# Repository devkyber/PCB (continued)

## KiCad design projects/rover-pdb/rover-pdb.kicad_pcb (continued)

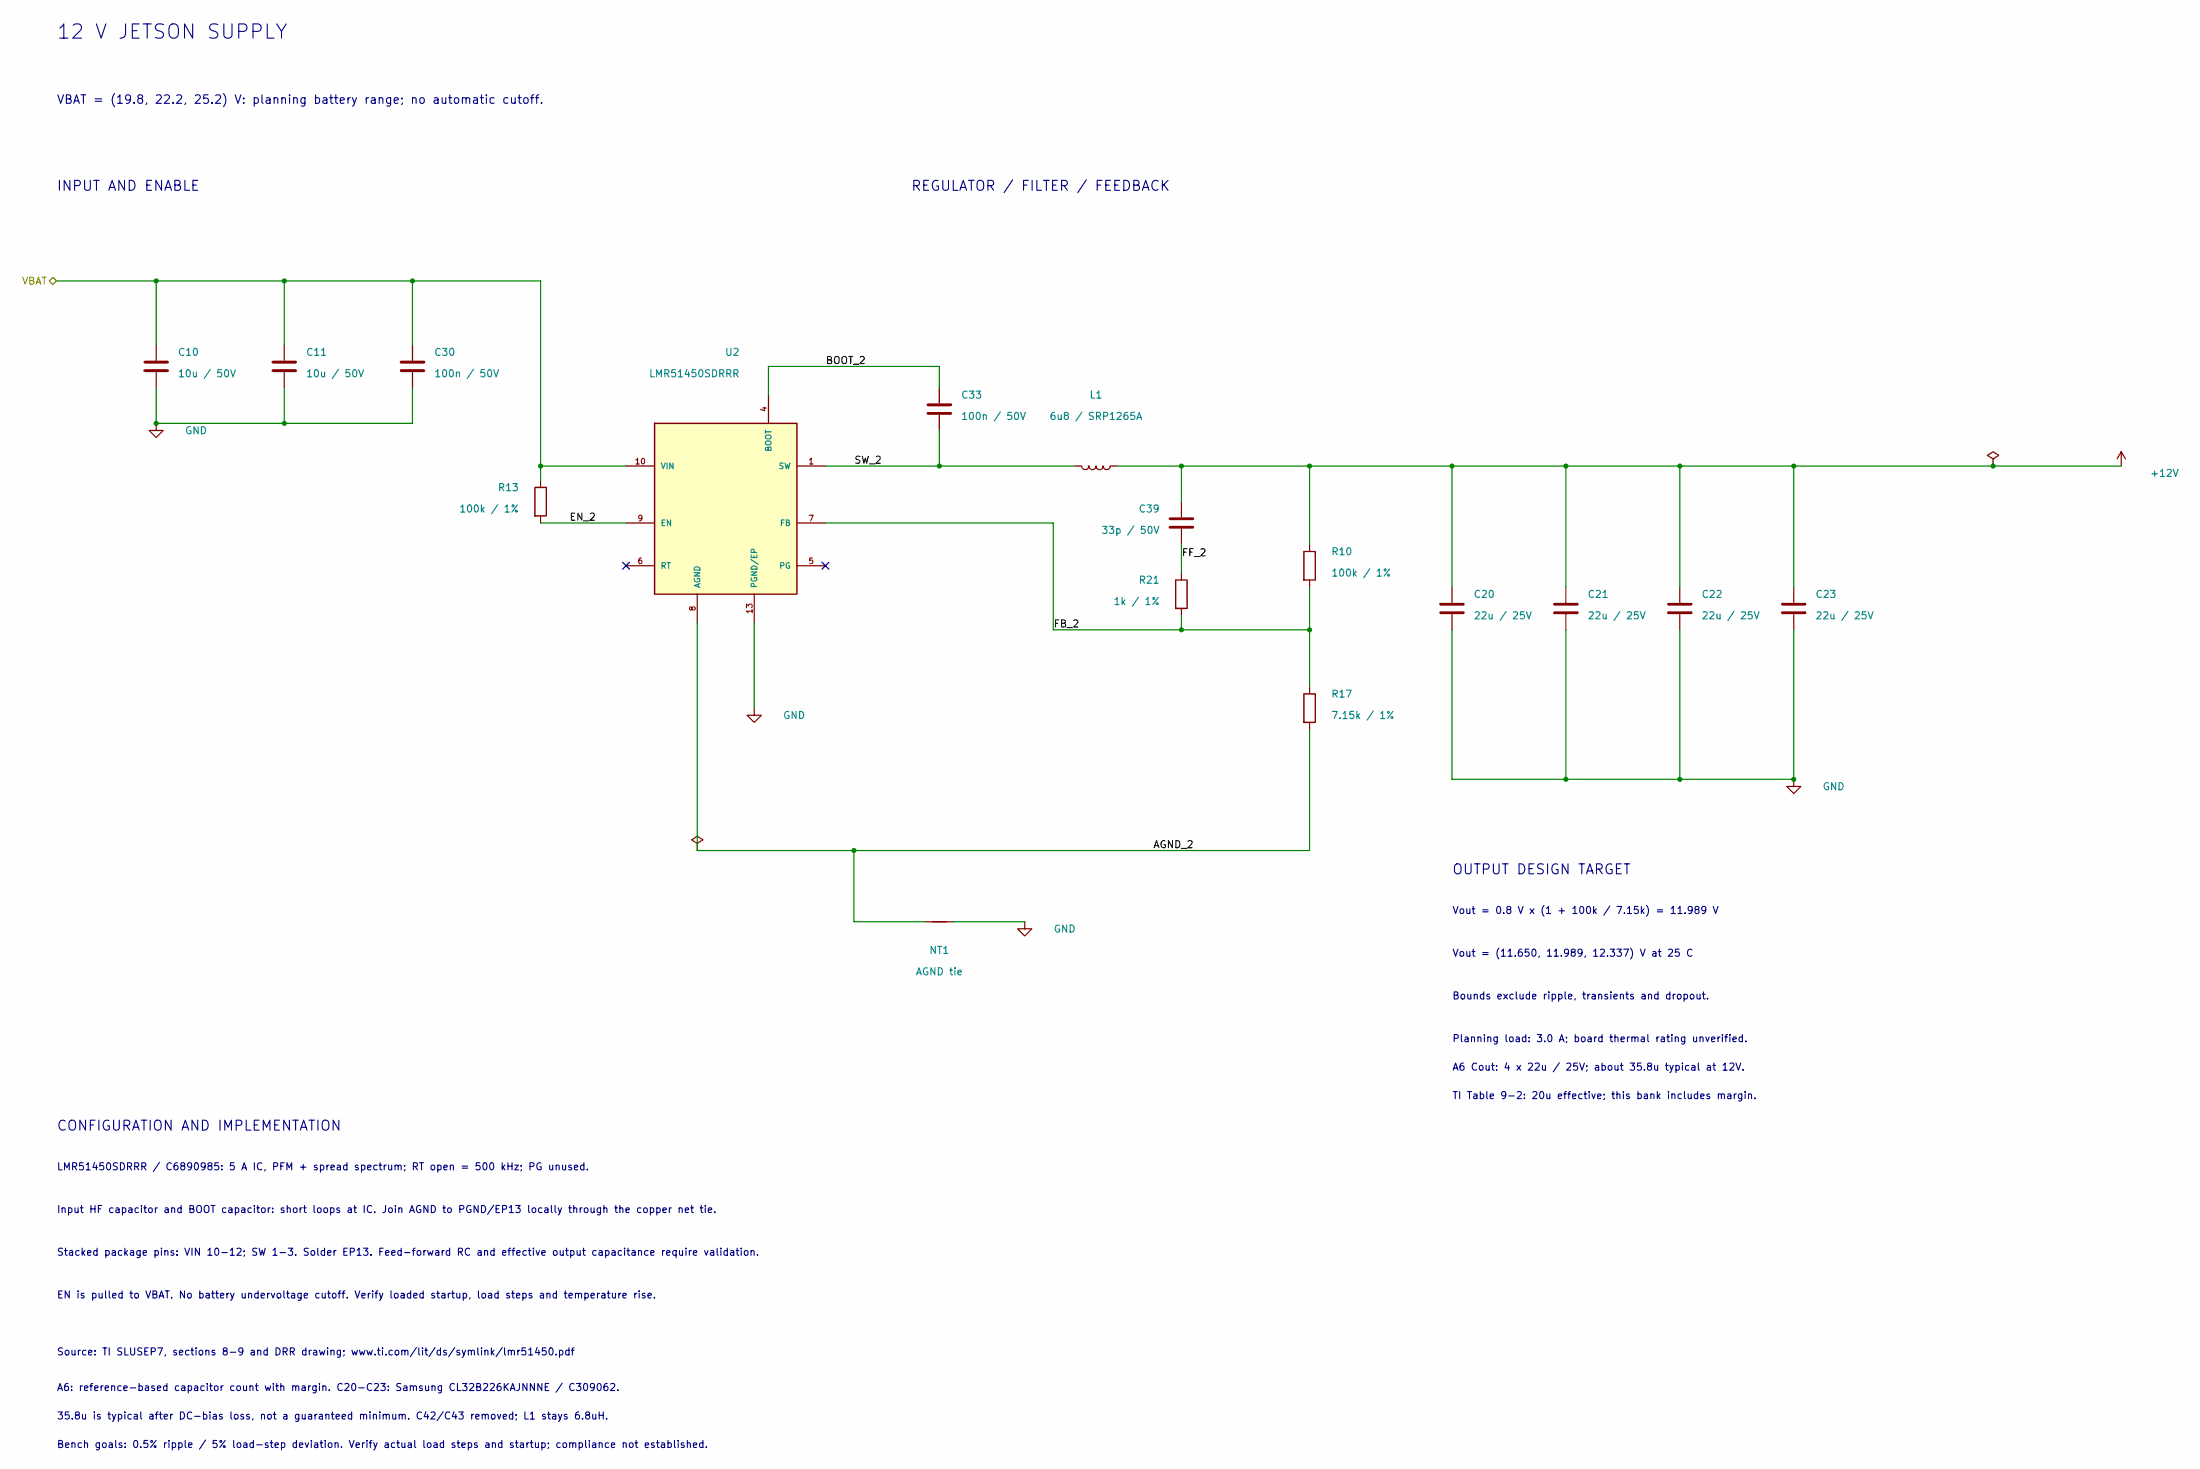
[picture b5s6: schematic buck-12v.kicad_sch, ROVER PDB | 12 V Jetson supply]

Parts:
C10, C11: 10u / 50V; C_1210_3225Metric; MPN GRM32ER71H106KA12L; LCSC Part C77102
C20, C21, C22, C23: 22u / 25V; C_1210_3225Metric; MPN CL32B226KAJNNNE; LCSC Part C309062
C30, C33: 100n / 50V; C_0805_2012Metric; MPN CL21B104KBCNNNC; LCSC Part C1711
C39: 33p / 50V; C_0603_1608Metric; MPN CL10C330JB8NNNC; LCSC Part C1663
L1: 6u8 / SRP1265A; SRP1265A_LeadFrame_13.5x12.5_P11.1; MPN SRP1265A-6R8M; LCSC Part C2041326
NT1: AGND tie; AGND_Tie_LMR51450
R10, R13: 100k / 1%; R_0805_2012Metric; MPN RC0805FR-07100KL; LCSC Part C96346
R17: 7.15k / 1%; R_0805_2012Metric; MPN 0805W8F7151T5E; LCSC Part C17806
R21: 1k / 1%; R_0805_2012Metric; MPN 0805W8F1001T5E; LCSC Part C17513
U2: LMR51450SDRRR; LMR51450_DRR_WSON12_3x3; MPN LMR51450SDRRR; LCSC Part C6890985

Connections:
+12V: C20.1, C21.1, C22.1, C23.1, C39.1, L1.1, R10.1; also elsewhere on the board
/12 V Jetson supply/AGND_2: NT1.1, R17.2, U2.8 (AGND)
/12 V Jetson supply/BOOT_2: C33.1, U2.4 (BOOT)
/12 V Jetson supply/EN_2: R13.2, U2.9 (EN)
/12 V Jetson supply/FB_2: R10.2, R17.1, R21.2, U2.7 (FB)
/12 V Jetson supply/FF_2: C39.2, R21.1
/12 V Jetson supply/SW_2: C33.2, L1.2, U2.1 (SW), U2.2 (SW), U2.3 (SW)
/VBAT: C10.1, C11.1, C30.1, R13.1, U2.10 (VIN), U2.11 (VIN), U2.12 (VIN); also elsewhere on the board
GND: C10.2, C11.2, C20.2, C21.2, C22.2, C23.2, C30.2, NT1.2, U2.13 (PGND/EP); also elsewhere on the board

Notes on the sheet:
Bounds exclude ripple, transients and dropout.
REGULATOR / FILTER / FEEDBACK
35.8u is typical after DC-bias loss, not a guaranteed minimum. C42/C43 removed; L1 stays 6.8uH.
EN is pulled to VBAT. No battery undervoltage cutoff. Verify loaded startup, load steps and temperature rise.
CONFIGURATION AND IMPLEMENTATION
A6 Cout: 4 x 22u / 25V; about 35.8u typical at 12V.
Vout = (11.650, 11.989, 12.337) V at 25 C
Bench goals: 0.5% ripple / 5% load-step deviation. Verify actual load steps and startup; compliance not established.
OUTPUT DESIGN TARGET
Vout = 0.8 V x (1 + 100k / 7.15k) = 11.989 V
A6: reference-based capacitor count with margin. C20-C23: Samsung CL32B226KAJNNNE / C309062.
INPUT AND ENABLE
Source: TI SLUSEP7, sections 8-9 and DRR drawing; www.ti.com/lit/ds/symlink/lmr51450.pdf
LMR51450SDRRR / C6890985: 5 A IC, PFM + spread spectrum; RT open = 500 kHz; PG unused.
12 V JETSON SUPPLY
VBAT = (19.8, 22.2, 25.2) V: planning battery range; no automatic cutoff.
Planning load: 3.0 A; board thermal rating unverified.
TI Table 9-2: 20u effective; this bank includes margin.
Stacked package pins: VIN 10-12; SW 1-3. Solder EP13. Feed-forward RC and effective output capacitance require validation.
Input HF capacitor and BOOT capacitor: short loops at IC. Join AGND to PGND/EP13 locally through the copper net tie.

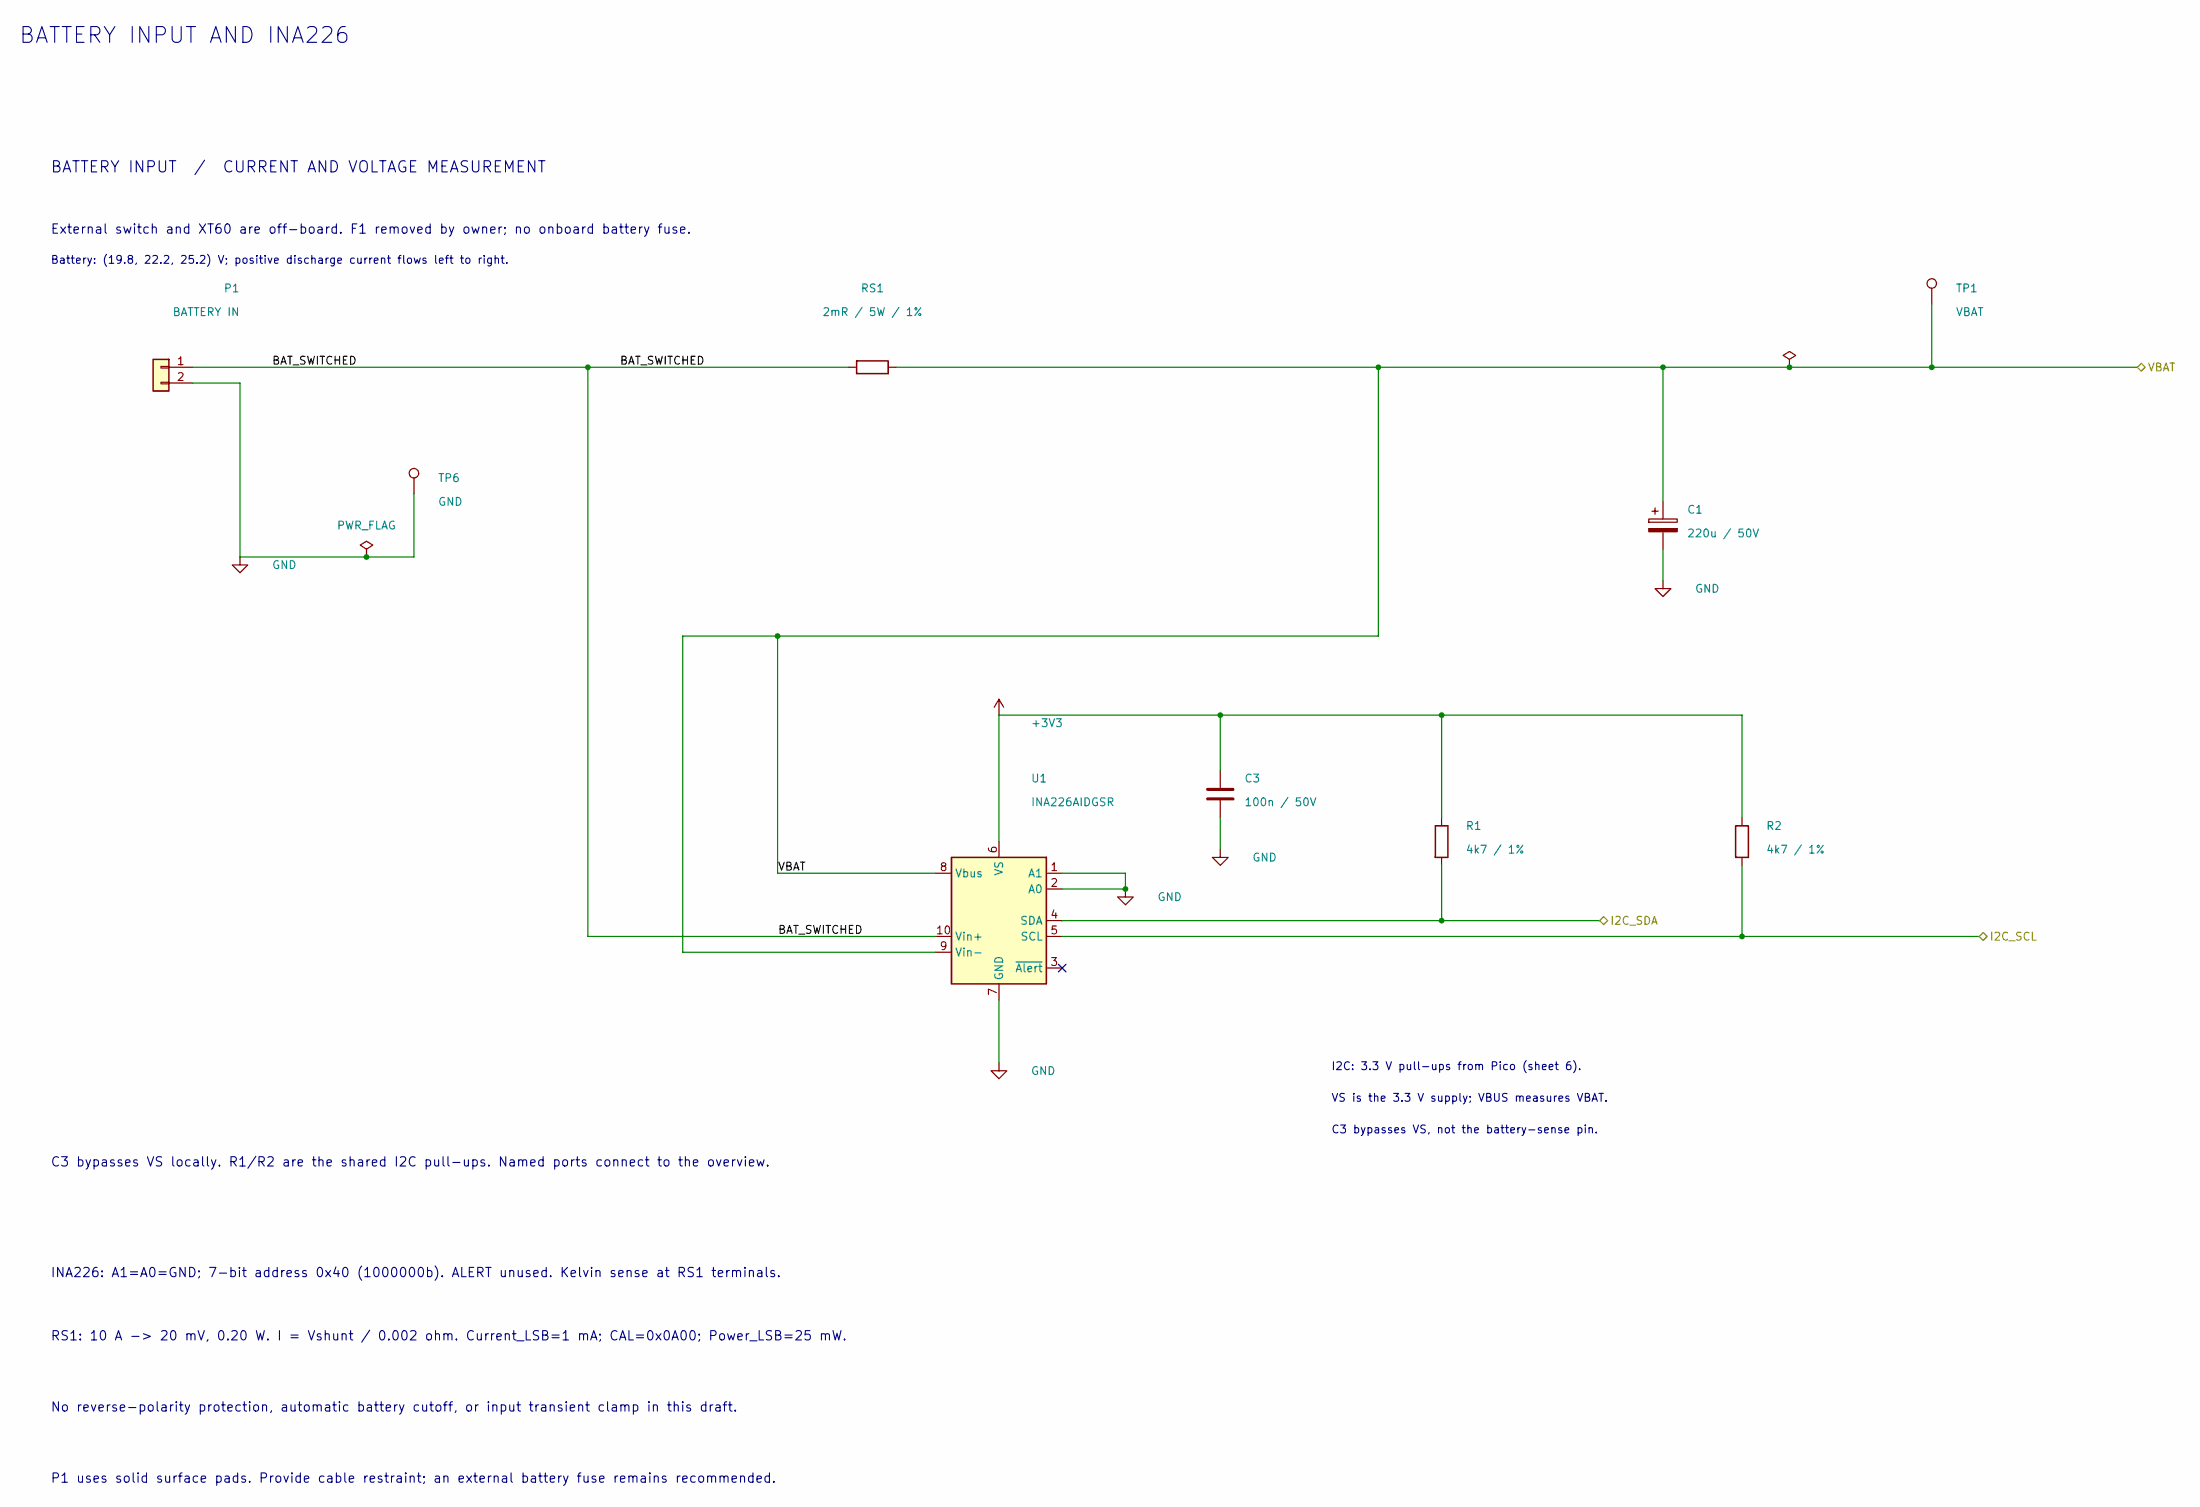
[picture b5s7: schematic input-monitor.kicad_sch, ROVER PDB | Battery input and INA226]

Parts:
C1: 220u / 50V; CP_Radial_D10.0mm_P5.00mm; MPN EEU-FR1H221B; LCSC Part C1579630
C3: 100n / 50V; C_0805_2012Metric; MPN CL21B104KBCNNNC; LCSC Part C1711
P1: BATTERY IN; WirePads_2_6x8_P12; MPN BATTERY IN
R1, R2: 4k7 / 1%; R_0805_2012Metric; MPN RC0805FR-074K7L; LCSC Part C60816
RS1: 2mR / 5W / 1%; CSS2H_2512_6.35x3.05; MPN CSS2H-2512K-2L00F; LCSC Part C2093761
TP1: VBAT; TestPoint_Pad_D2.0mm; MPN VBAT
TP6: GND; TestPoint_Pad_D2.0mm; MPN GND
U1: INA226AIDGSR; MSOP-10_3x3mm_P0.5mm; MPN INA226AIDGSR; LCSC Part C49851

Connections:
+3V3: C3.1, R1.1, R2.1, U1.6 (VS); also elsewhere on the board
/Battery input and INA226/BAT_SWITCHED: P1.1, RS1.2, U1.10 (Vin+)
/Battery input and INA226/I2C_SCL: R2.2, U1.5 (SCL); also elsewhere on the board
/Battery input and INA226/I2C_SDA: R1.2, U1.4 (SDA); also elsewhere on the board
/VBAT: C1.1, RS1.1, TP1.1 (1_1), U1.8 (Vbus), U1.9 (Vin-); also elsewhere on the board
GND: C1.2, C3.2, P1.2, TP6.1 (1_1), U1.1 (A1), U1.2 (A0), U1.7 (GND); also elsewhere on the board

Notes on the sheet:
RS1: 10 A -> 20 mV, 0.20 W. I = Vshunt / 0.002 ohm. Current_LSB=1 mA; CAL=0x0A00; Power_LSB=25 mW.
INA226: A1=A0=GND; 7-bit address 0x40 (1000000b). ALERT unused. Kelvin sense at RS1 terminals.
BATTERY INPUT AND INA226
C3 bypasses VS locally. R1/R2 are the shared I2C pull-ups. Named ports connect to the overview.
Battery: (19.8, 22.2, 25.2) V; positive discharge current flows left to right.
No reverse-polarity protection, automatic battery cutoff, or input transient clamp in this draft.
I2C: 3.3 V pull-ups from Pico (sheet 6).
C3 bypasses VS, not the battery-sense pin.
External switch and XT60 are off-board. F1 removed by owner; no onboard battery fuse.
BATTERY INPUT / CURRENT AND VOLTAGE MEASUREMENT
P1 uses solid surface pads. Provide cable restraint; an external battery fuse remains recommended.
VS is the 3.3 V supply; VBUS measures VBAT.

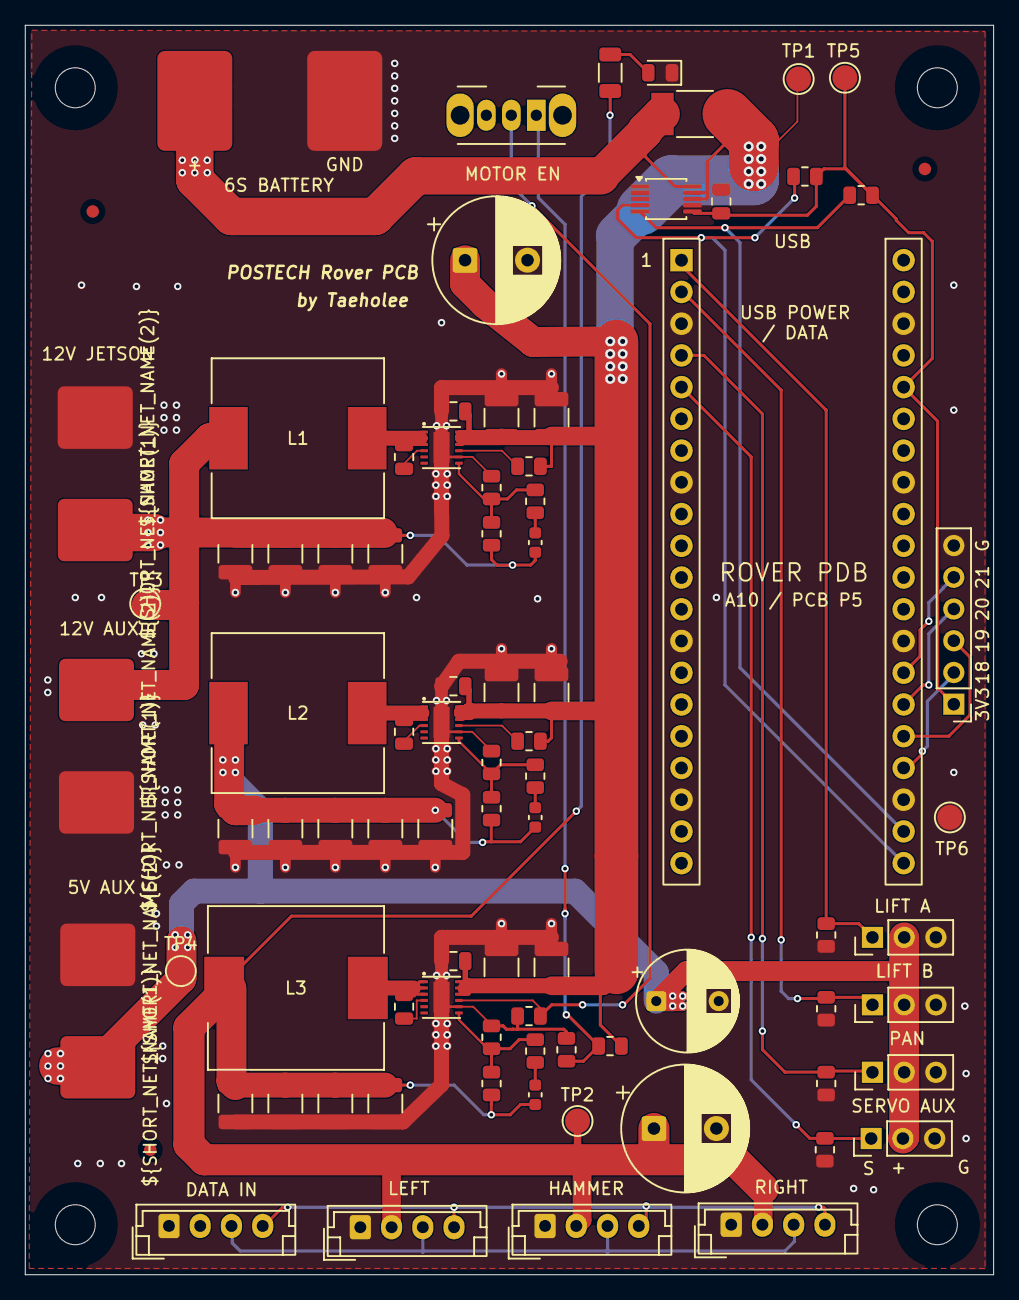
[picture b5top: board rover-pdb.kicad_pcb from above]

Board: 2 copper layers, 77.5 x 100.0 mm, 93 parts (0 on the bottom side), 39 nets.

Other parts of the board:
FID1, FID2, FID3: Fiducial; Fiducial_1mm_Mask2mm
H1, H2, H3, H4: MountingHole_3.2mm_M3

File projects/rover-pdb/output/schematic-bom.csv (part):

Reference,Value,MPN,LCSC,Footprint,DNP,InBOM,Sheet
C1,220u / 50V,EEU-FR1H221B,C1579630,Capacitor_THT:CP_Radial_D10.0mm_P5.00mm,no,yes,input-monitor.kicad_sch
C2,470u / 16V,EEU-FR1C471B,C1579437,Capacitor_THT:CP_Radial_D8.0mm_P5.00mm,no,yes,pico-servos.kicad_sch
C3,100n / 50V,CL21B104KBCNNNC,C1711,Capacitor_SMD:C_0805_2012Metric,no,yes,input-monitor.kicad_sch
C5,220u / 50V,EEU-FR1H221B,C1579630,Capacitor_THT:CP_Radial_D10.0mm_P5.00mm,no,yes,buck-motor.kicad_sch
C10,10u / 50V,GRM32ER71H106KA12L,C77102,Capacitor_SMD:C_1210_3225Metric,no,yes,buck-12v.kicad_sch
C11,10u / 50V,GRM32ER71H106KA12L,C77102,Capacitor_SMD:C_1210_3225Metric,no,yes,buck-12v.kicad_sch
C12,10u / 50V,GRM32ER71H106KA12L,C77102,Capacitor_SMD:C_1210_3225Metric,no,yes,buck-5v.kicad_sch
C13,10u / 50V,GRM32ER71H106KA12L,C77102,Capacitor_SMD:C_1210_3225Metric,no,yes,buck-5v.kicad_sch
C14,10u / 50V,GRM32ER71H106KA12L,C77102,Capacitor_SMD:C_1210_3225Metric,no,yes,buck-motor.kicad_sch
C15,10u / 50V,GRM32ER71H106KA12L,C77102,Capacitor_SMD:C_1210_3225Metric,no,yes,buck-motor.kicad_sch
C16,10u / 50V,GRM32ER71H106KA12L,C77102,Capacitor_SMD:C_1210_3225Metric,no,yes,buck-motor.kicad_sch
C17,10u / 50V,GRM32ER71H106KA12L,C77102,Capacitor_SMD:C_1210_3225Metric,no,yes,buck-motor.kicad_sch
C18,10u / 50V,GRM32ER71H106KA12L,C77102,Capacitor_SMD:C_1210_3225Metric,no,yes,buck-motor.kicad_sch
C19,10u / 50V,GRM32ER71H106KA12L,C77102,Capacitor_SMD:C_1210_3225Metric,no,yes,buck-motor.kicad_sch
C20,22u / 25V,CL32B226KAJNNNE,C309062,Capacitor_SMD:C_1210_3225Metric,no,yes,buck-12v.kicad_sch
C21,22u / 25V,CL32B226KAJNNNE,C309062,Capacitor_SMD:C_1210_3225Metric,no,yes,buck-12v.kicad_sch
C22,22u / 25V,CL32B226KAJNNNE,C309062,Capacitor_SMD:C_1210_3225Metric,no,yes,buck-12v.kicad_sch
C23,22u / 25V,CL32B226KAJNNNE,C309062,Capacitor_SMD:C_1210_3225Metric,no,yes,buck-12v.kicad_sch
C24,22u / 25V,CL32B226KAJNNNE,C309062,Capacitor_SMD:C_1210_3225Metric,no,yes,buck-5v.kicad_sch
C25,22u / 25V,CL32B226KAJNNNE,C309062,Capacitor_SMD:C_1210_3225Metric,no,yes,buck-5v.kicad_sch
C26,22u / 25V,CL32B226KAJNNNE,C309062,Capacitor_SMD:C_1210_3225Metric,no,yes,buck-5v.kicad_sch
C27,22u / 25V,CL32B226KAJNNNE,C309062,Capacitor_SMD:C_1210_3225Metric,no,yes,buck-5v.kicad_sch
C28,22u / 25V,CL32B226KAJNNNE,C309062,Capacitor_SMD:C_1210_3225Metric,no,yes,buck-5v.kicad_sch
C30,100n / 50V,CL21B104KBCNNNC,C1711,Capacitor_SMD:C_0805_2012Metric,no,yes,buck-12v.kicad_sch
C31,100n / 50V,CL21B104KBCNNNC,C1711,Capacitor_SMD:C_0805_2012Metric,no,yes,buck-5v.kicad_sch
C32,100n / 50V,CL21B104KBCNNNC,C1711,Capacitor_SMD:C_0805_2012Metric,no,yes,buck-motor.kicad_sch
C33,100n / 50V,CL21B104KBCNNNC,C1711,Capacitor_SMD:C_0805_2012Metric,no,yes,buck-12v.kicad_sch
C34,100n / 50V,CL21B104KBCNNNC,C1711,Capacitor_SMD:C_0805_2012Metric,no,yes,buck-5v.kicad_sch
C35,100n / 50V,CL21B104KBCNNNC,C1711,Capacitor_SMD:C_0805_2012Metric,no,yes,buck-motor.kicad_sch
C39,33p / 50V,CL10C330JB8NNNC,C1663,Capacitor_SMD:C_0603_1608Metric,no,yes,buck-12v.kicad_sch
C40,33p / 50V,CL10C330JB8NNNC,C1663,Capacitor_SMD:C_0603_1608Metric,no,yes,buck-5v.kicad_sch
C41,33p / 50V,CL10C330JB8NNNC,C1663,Capacitor_SMD:C_0603_1608Metric,no,yes,buck-motor.kicad_sch
D2,GREEN,KT-0805G,C2297,rover:KT0805G_0805_A1_K2,no,yes,buck-motor.kicad_sch
J1,U2D2 DATA IN,B4B-EH-A(LF)(SN),C160258,Connector_JST:JST_EH_B4B-EH-A_1x04_P2.50mm_Vertical,no,yes,dxl-enable.kicad_sch
J2,LIFT A,TSW-103-07-G-S,C3335811,Connector_PinHeader_2.54mm:PinHeader_1x03_P2.54mm_Vertical,no,yes,pico-servos.kicad_sch
J3,LIFT B,TSW-103-07-G-S,C3335811,Connector_PinHeader_2.54mm:PinHeader_1x03_P2.54mm_Vertical,no,yes,pico-servos.kicad_sch
J4,CAMERA PAN,TSW-103-07-G-S,C3335811,Connector_PinHeader_2.54mm:PinHeader_1x03_P2.54mm_Vertical,no,yes,pico-servos.kicad_sch
J5,LEFT WHEELS,B4B-EH-A(LF)(SN),C160258,Connector_JST:JST_EH_B4B-EH-A_1x04_P2.50mm_Vertical,no,yes,dxl-enable.kicad_sch
J6,RIGHT WHEELS,B4B-EH-A(LF)(SN),C160258,Connector_JST:JST_EH_B4B-EH-A_1x04_P2.50mm_Vertical,no,yes,dxl-enable.kicad_sch
J7,HAMMER,B4B-EH-A(LF)(SN),C160258,Connector_JST:JST_EH_B4B-EH-A_1x04_P2.50mm_Vertical,no,yes,dxl-enable.kicad_sch
J9,EXP / DNP,2.54-1x6P直针,C37208,Connector_PinHeader_2.54mm:PinHeader_1x06_P2.54mm_Vertical,yes,yes,pico-servos.kicad_sch
L1,6u8 / SRP1265A,SRP1265A-6R8M,C2041326,rover:SRP1265A_LeadFrame_13.5x12.5_P11.1,no,yes,buck-12v.kicad_sch
L2,4u7 / SRP1265A,SRP1265A-4R7M,C780205,rover:SRP1265A_LeadFrame_13.5x12.5_P11.1,no,yes,buck-5v.kicad_sch
L3,3u3 / SRP1265A,SRP1265A-3R3M,C1329348,rover:SRP1265A_LeadFrame_13.5x12.5_P11.1,no,yes,buck-motor.kicad_sch
NT1,AGND tie,,,rover:AGND_Tie_LMR51450,no,no,buck-12v.kicad_sch
NT2,AGND tie,,,rover:AGND_Tie_LMR51450,no,no,buck-5v.kicad_sch
NT3,AGND tie,,,rover:AGND_Tie_LMR51450,no,no,buck-motor.kicad_sch
P1,BATTERY IN,BATTERY IN,,rover:WirePads_2_6x8_P12,no,no,input-monitor.kicad_sch
P2,JETSON / BARREL,JETSON / BARREL,,rover:WirePads_2_5x6_P9,no,no,pico-servos.kicad_sch
P3,12V EXP / UNWIRED,12V EXP / UNWIRED,,rover:WirePads_2_5x6_P9,no,no,pico-servos.kicad_sch
P4,5V EXP / UNWIRED,5V EXP / UNWIRED,,rover:WirePads_2_5x6_P9,no,no,pico-servos.kicad_sch
R1,4k7 / 1%,RC0805FR-074K7L,C60816,Resistor_SMD:R_0805_2012Metric,no,yes,input-monitor.kicad_sch
R2,4k7 / 1%,RC0805FR-074K7L,C60816,Resistor_SMD:R_0805_2012Metric,no,yes,input-monitor.kicad_sch
R3,10k,RC0805FR-0710KL,C84376,Resistor_SMD:R_0805_2012Metric,no,yes,pico-servos.kicad_sch
R4,10k,RC0805FR-0710KL,C84376,Resistor_SMD:R_0805_2012Metric,no,yes,pico-servos.kicad_sch
R5,10k,RC0805FR-0710KL,C84376,Resistor_SMD:R_0805_2012Metric,no,yes,pico-servos.kicad_sch
R10,100k / 1%,RC0805FR-07100KL,C96346,Resistor_SMD:R_0805_2012Metric,no,yes,buck-12v.kicad_sch
R11,100k / 1%,RC0805FR-07100KL,C96346,Resistor_SMD:R_0805_2012Metric,no,yes,buck-5v.kicad_sch
R12,100k / 1%,RC0805FR-07100KL,C96346,Resistor_SMD:R_0805_2012Metric,no,yes,buck-motor.kicad_sch
R13,100k / 1%,RC0805FR-07100KL,C96346,Resistor_SMD:R_0805_2012Metric,no,yes,buck-12v.kicad_sch
R14,100k / 1%,RC0805FR-07100KL,C96346,Resistor_SMD:R_0805_2012Metric,no,yes,buck-5v.kicad_sch
R15,100k / 1%,RC0805FR-07100KL,C96346,Resistor_SMD:R_0805_2012Metric,no,yes,buck-motor.kicad_sch
R16,19.1k / 1%,0805W8F1912T5E,C17508,Resistor_SMD:R_0805_2012Metric,no,yes,buck-5v.kicad_sch
R17,7.15k / 1%,0805W8F7151T5E,C17806,Resistor_SMD:R_0805_2012Metric,no,yes,buck-12v.kicad_sch
R18,3.74k / 1%,0805W8F3741T5E,C65649,Resistor_SMD:R_0805_2012Metric,no,yes,buck-motor.kicad_sch
R19,100k / 1%,RC0805FR-07100KL,C96346,Resistor_SMD:R_0805_2012Metric,no,yes,buck-motor.kicad_sch
R20,3k9 / 0.25W,RC1206FR-073K9L,C137289,Resistor_SMD:R_1206_3216Metric,no,yes,buck-motor.kicad_sch
R21,1k / 1%,0805W8F1001T5E,C17513,Resistor_SMD:R_0805_2012Metric,no,yes,buck-12v.kicad_sch
R22,1k / 1%,0805W8F1001T5E,C17513,Resistor_SMD:R_0805_2012Metric,no,yes,buck-5v.kicad_sch
R23,1k / 1%,0805W8F1001T5E,C17513,Resistor_SMD:R_0805_2012Metric,no,yes,buck-motor.kicad_sch
R24,22k / 1%,0805W8F2202T5E,C17560,Resistor_SMD:R_0805_2012Metric,no,yes,buck-motor.kicad_sch
RS1,2mR / 5W / 1%,CSS2H-2512K-2L00F,C2093761,rover:CSS2H_2512_6.35x3.05,no,yes,input-monitor.kicad_sch
SKT1,Pico 2 / 2x20 sockets,Pico 2,,rover:Pico2_Sockets_LXWCONN_254PM_1x20,no,yes,pico-servos.kicad_sch
SW1,MOTOR ENABLE,OS102011MA1QN1,C226259,Button_Switch_THT:SW_Slide_SPDT_Angled_CK_OS102011MA1Q,no,yes,buck-motor.kicad_sch
TP1,VBAT,VBAT,,TestPoint:TestPoint_Pad_D2.0mm,no,no,input-monitor.kicad_sch
TP2,VMOTOR,VMOTOR,,TestPoint:TestPoint_Pad_D2.0mm,no,no,buck-motor.kicad_sch
TP3,+12V,+12V,,TestPoint:TestPoint_Pad_D2.0mm,no,no,pico-servos.kicad_sch
TP4,+5V,+5V,,TestPoint:TestPoint_Pad_D2.0mm,no,no,pico-servos.kicad_sch
TP5,+3V3,+3V3,,TestPoint:TestPoint_Pad_D2.0mm,no,no,pico-servos.kicad_sch
TP6,GND,GND,,TestPoint:TestPoint_Pad_D2.0mm,no,no,input-monitor.kicad_sch
U1,INA226AIDGSR,INA226AIDGSR,C49851,Package_SO:MSOP-10_3x3mm_P0.5mm,no,yes,input-monitor.kicad_sch
U2,LMR51450SDRRR,LMR51450SDRRR,C6890985,rover:LMR51450_DRR_WSON12_3x3,no,yes,buck-12v.kicad_sch
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
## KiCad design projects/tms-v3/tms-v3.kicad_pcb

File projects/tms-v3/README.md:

# TMS v3: rework starting point

Open [tms-v3.kicad_pro](tms-v3.kicad_pro). The saved seven-sheet schematic and
PCB are the owner's current files. The 2026-10-07 workspace cleanup preserved
their bytes and established the audit below; no circuit or routing repair was
applied. Read [requirements](REQUIREMENTS.md), [design basis](DESIGN_BASIS.md),
[deviations](DEVIATIONS.md), [reference review](REFERENCE_REVIEW.md) and
[review profile](review-profile.yaml) before choosing the next change.

## Current audit: 2026-10-07

The [full shared review](docs/review/records/rework-baseline-20261007.json)
reports seven passing checks and seven blockers. The
[native ERC report](docs/review/records/erc-20261007.json) preserves the individual
findings. These reports describe saved CAD, not an approved design.

| Check | Result |
| --- | --- |
| Source integrity | Research and archived datasheets pass |
| ERC | 2 disconnected-pin errors and 3 dangling-wire warnings; 37 unspecified-pin warnings excluded by the existing policy |
| Saved connectivity snapshot | Stale for two components; current schematic and PCB disagree |
| Forward annotation | PCB schematic links are absent; ordinary F8 updating is not yet a safe handover |
| Native DRC | 1 error, 15 warnings and 4 unconnected items in both refilled runs |
| Independent manufacturing baseline | 244 errors and 4 unconnected items against the dated JLCPCB profile; includes settings, annular-ring, clearance and silk findings |
| Assembly contract | J1/J2 have conflicting values without exact MPN identity |
| Routing topology | 55 short-track and 3 covered-track advisories; these require local inspection, not automatic deletion |
| Human decisions | 0/12 current decisions, including the two mandatory shared items |

## Visual inspection of the saved schematic

All seven native PDF pages were inspected at full-page and circuit scale on
2026-10-07. This is author inspection, not an owner's release decision.
The exact render and its source hashes are recorded in
[visual provenance](docs/review/records/visual-baseline-20261007.json).

| Sheet | Remaining presentation issues |
| --- | --- |
| Overview | Six small hierarchy boxes occupy a narrow column on a mostly empty A1 page; there is no readable system-level power/interface flow or load summary |
| Power and protection | Power assertions are detached; some wiring visually approaches terminals without agreeing with native connectivity; assumptions are absent |
| Load cell / ADS1256 | Bypass, reference, clock and interface groups rely on matching detached labels; pin arrangement follows the package rather than the signal flow |
| Pressure / ADS1220 | Input and interface parts are remote from the IC; bypass parts use detached rail groups; most of the sheet is unused |
| Controller and telemetry | Long socket pin lists and labels dominate; bypass parts and the power assertion are detached; module/interface roles need clearer grouping |
| Ignition control | Sparse groups and labels make page flow difficult to follow; native ERC reports an unresolved disconnected terminal; no functional change was made |
| External connectors and test | Connectors and test points are separated into label lists; destination context and documented electrical assumptions are missing |

Titles and hierarchy are present. That does not establish readability or
electrical agreement. Follow the shared Gala/Gross conventions for any authorized
presentation work, and prove unchanged native pin/net and explicit-NC membership.

## Continue from this state

The [2026-10-07 pipeline validation](docs/review/pipeline-validation-20261007.md)
ran 25 CLI commands on disposable copies through research, import, native
previews, blocked application, review, sign-off preparation, release and cleanup.
The expected blocking and preservation checks passed. TMS remains blocked;
J1/J2 part identity prevents even a completed quotation preview. The report
states which successful export/publication paths could not be reached.

First reconcile which saved circuit is intended before updating the netmap or
PCB links. A drawing-only edit cannot silently repair a circuit discrepancy.
Then prepare a scoped native candidate and inspect every changed sheet using
the [shared workflow](../../docs/WORKFLOW.md). Do not replay the old intent over
owner edits, discard routing or silence findings by broadening deviations.

The original PDR and Rev D BOM remain historical requirements evidence, not
current production instructions. The open engineering decisions remain in the
existing requirements/profile; the cleanup and this audit resolve none of them.
Layout, assembly and release stay blocked pending their respective checks.

```powershell
uv run pcb-copilot status projects/tms-v3
uv run pcb-copilot research projects/tms-v3 --verify
uv run pcb-copilot review projects/tms-v3
```

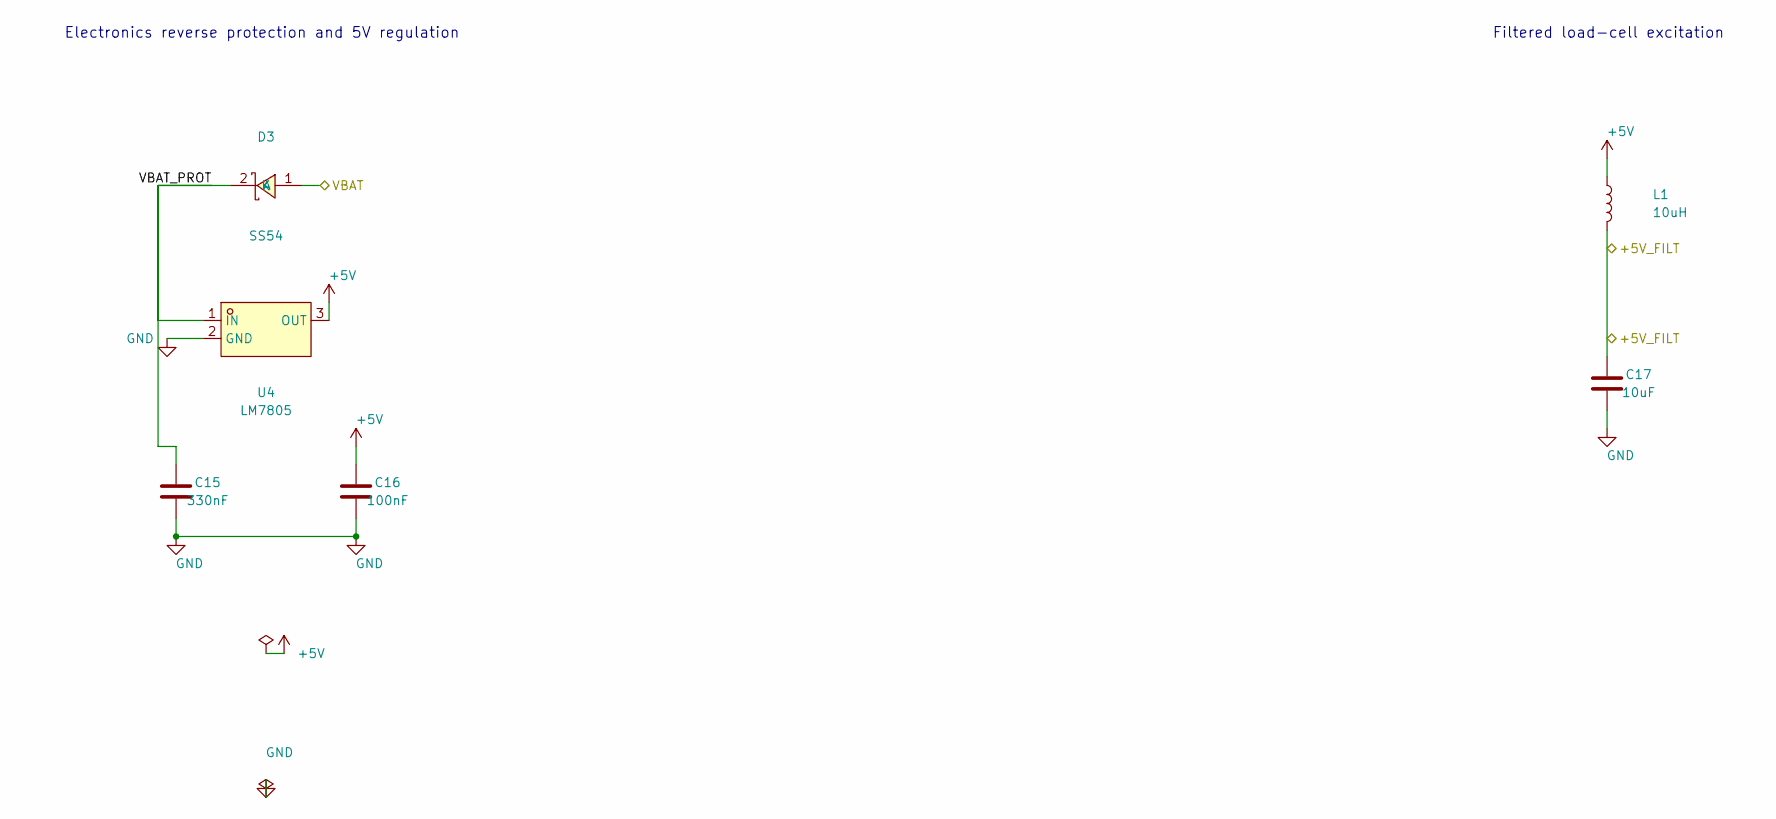
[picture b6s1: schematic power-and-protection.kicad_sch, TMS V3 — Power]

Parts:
C15: 330nF; C_0603_1608Metric
C16: 100nF; C_0603_1608Metric
C17: 10uF; C_0805_2012Metric
D3: SS54; SMA_L4.4-W2.8-LS5.4-R-RD
L1: 10uH; L_0805_2012Metric
U4: LM7805; TO-263-2_L10.1-W9.1-P5.08-LS15.2-BR-1

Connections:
+5V: C16.1, L1.1, U4.3 (OUT); also elsewhere on the board
+5V_FILT: C17.1, L1.2; also elsewhere on the board
GND: C15.2, C16.2, C17.2, U4.2 (GND); also elsewhere on the board
Power/VBAT_PROT: C15.1, D3.2 (K), U4.1 (IN)
VBAT: D3.1 (A); also elsewhere on the board

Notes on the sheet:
Electronics reverse protection and 5V regulation
Filtered load-cell excitation

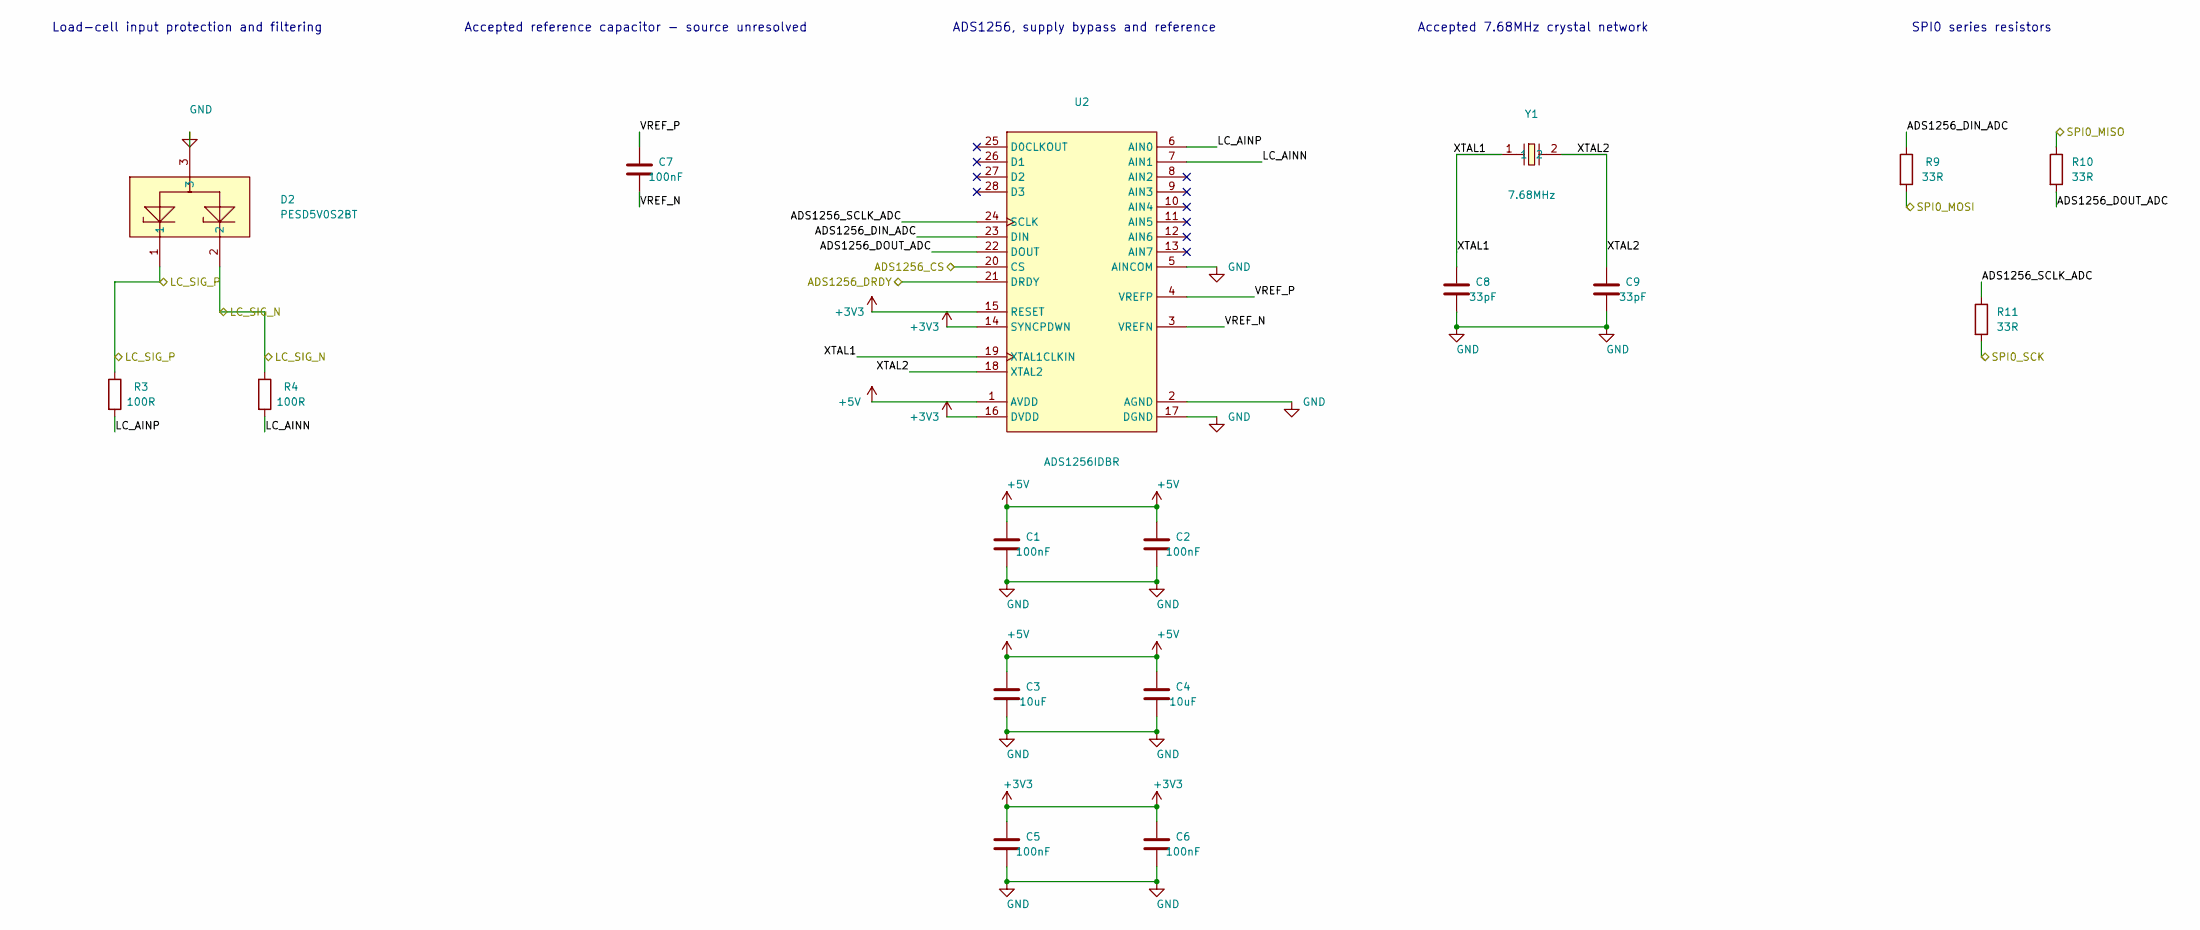
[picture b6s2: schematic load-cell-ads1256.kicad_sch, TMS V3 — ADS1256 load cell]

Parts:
C1, C2, C5, C6, C7: 100nF; C_0603_1608Metric
C3, C4: 10uF; C_0805_2012Metric
C8, C9: 33pF; C_0402_1005Metric
D2: PESD5V0S2BT; SOT-23_L2.9-W1.3-P1.90-LS2.4-BR
R3, R4: 100R; R_0402_1005Metric
R9, R10, R11: 33R; R_0402_1005Metric
U2: ADS1256IDBR; SSOP-28_L10.2-W5.3-P0.65-LS7.8-BL
Y1: 7.68MHz; CRYSTAL-SMD_L11.4-W4.7-LS12.4

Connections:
+3V3: C5.1, C6.1, U2.14 (SYNCPDWN), U2.15 (RESET), U2.16 (DVDD); also elsewhere on the board
+5V: C1.1, C2.1, C3.1, C4.1, U2.1 (AVDD); also elsewhere on the board
ADS1256 load cell/ADS1256_DIN_ADC: R9.1, U2.23 (DIN)
ADS1256 load cell/ADS1256_DOUT_ADC: R10.2, U2.22 (DOUT)
ADS1256 load cell/ADS1256_SCLK_ADC: R11.1, U2.24 (SCLK)
ADS1256 load cell/LC_AINN: R4.2, U2.7 (AIN1)
ADS1256 load cell/LC_AINP: R3.2, U2.6 (AIN0)
ADS1256 load cell/VREF_N: C7.2, U2.3 (VREFN)
ADS1256 load cell/VREF_P: C7.1, U2.4 (VREFP)
ADS1256 load cell/XTAL1: C8.1, U2.19 (XTAL1CLKIN), Y1.1
ADS1256 load cell/XTAL2: C9.1, U2.18 (XTAL2), Y1.2
ADS1256_CS: U2.20 (CS); also elsewhere on the board
ADS1256_DRDY: U2.21 (DRDY); also elsewhere on the board
GND: C1.2, C2.2, C3.2, C4.2, C5.2, C6.2, C8.2, C9.2, D2.3, U2.2 (AGND), U2.5 (AINCOM), U2.17 (DGND); also elsewhere on the board
LC_SIG_N: D2.2, R4.1; also elsewhere on the board
LC_SIG_P: D2.1, R3.1; also elsewhere on the board
SPI0_MISO: R10.1; also elsewhere on the board
SPI0_MOSI: R9.2; also elsewhere on the board
SPI0_SCK: R11.2; also elsewhere on the board

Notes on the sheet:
Load-cell input protection and filtering
Accepted reference capacitor - source unresolved
ADS1256, supply bypass and reference
Accepted 7.68MHz crystal network
SPI0 series resistors
